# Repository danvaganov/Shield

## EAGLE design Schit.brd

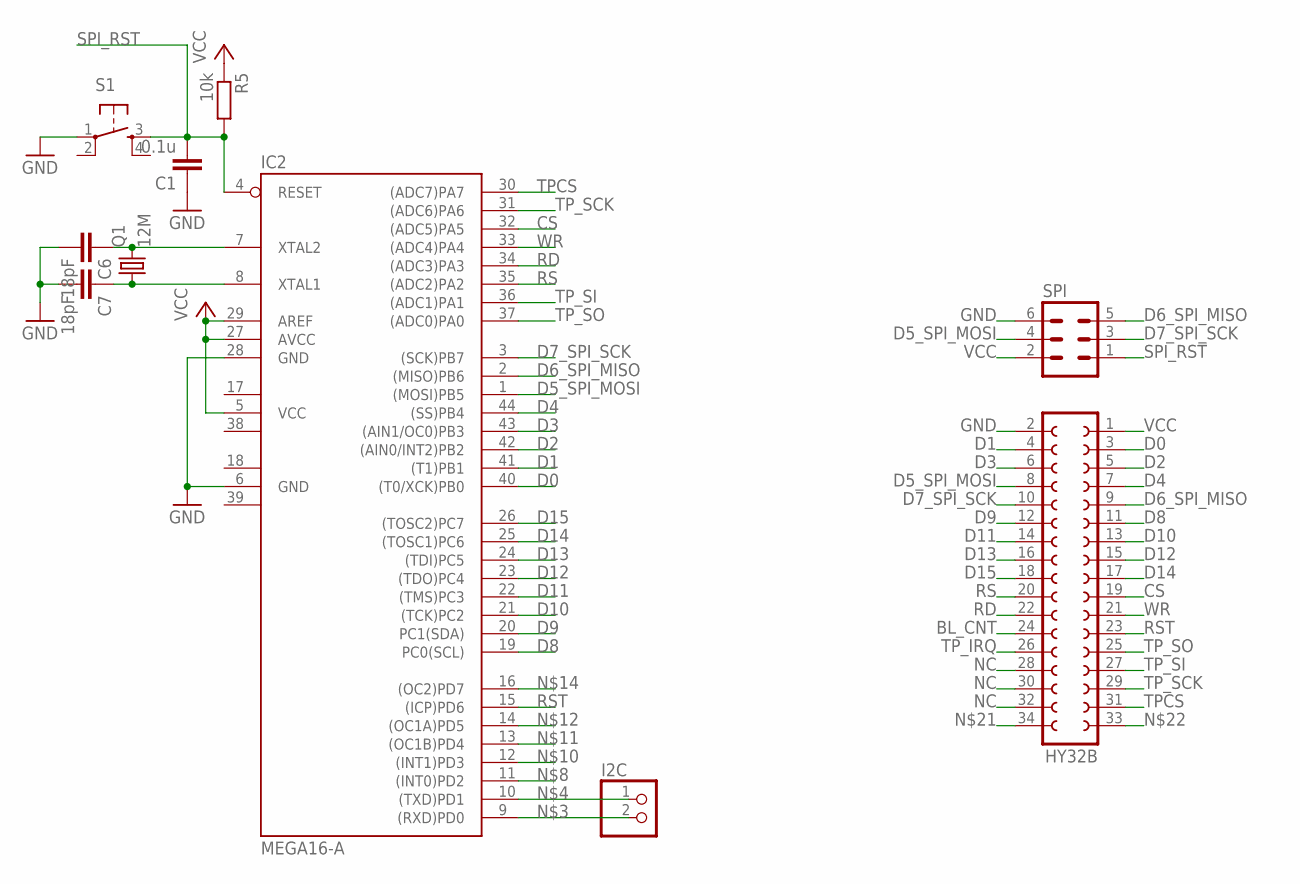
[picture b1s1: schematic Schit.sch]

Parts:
C1: 0.1u; C0805
C6, C7: 18pF; C0805
HY32B: FE17-2
I2C: PINHD-1X2; 1X02
IC2: MEGA16-A; TQFP44
Q1: 12M; HC49/S
R5: 10k; R0805
S1: TAC_SWITCHSMD; TACTILE_SWITCH_SMD
SPI: ML6

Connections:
BL_CNT: HY32B.24
CS: HY32B.19, IC2.32 ((ADC5)PA5)
D0: HY32B.3, IC2.40 ((T0/XCK)PB0)
D1: HY32B.4, IC2.41 ((T1)PB1)
D2: HY32B.5, IC2.42 ((AIN0/INT2)PB2)
D3: HY32B.6, IC2.43 ((AIN1/OC0)PB3)
D4: HY32B.7, IC2.44 ((SS)PB4)
D5_SPI_MOSI: HY32B.8, IC2.1 ((MOSI)PB5), SPI.4
D6_SPI_MISO: HY32B.9, IC2.2 ((MISO)PB6), SPI.5
D7_SPI_SCK: HY32B.10, IC2.3 ((SCK)PB7), SPI.3
D8: HY32B.11, IC2.19 (PC0(SCL))
D9: HY32B.12, IC2.20 (PC1(SDA))
D10: HY32B.13, IC2.21 ((TCK)PC2)
D11: HY32B.14, IC2.22 ((TMS)PC3)
D12: HY32B.15, IC2.23 ((TDO)PC4)
D13: HY32B.16, IC2.24 ((TDI)PC5)
D14: HY32B.17, IC2.25 ((TOSC1)PC6)
D15: HY32B.18, IC2.26 ((TOSC2)PC7)
GND: C1.1, C6.2, C7.2, HY32B.2, IC2.6 (GND), IC2.28 (GND), S1.1, SPI.6
GND1: IC2.18 (GND1)
GND2: IC2.39 (GND2)
unnamed: I2C.2, IC2.9 ((RXD)PD0)
unnamed: I2C.1, IC2.10 ((TXD)PD1)
unnamed: C7.1, IC2.8 (XTAL1), Q1.1
NC: HY32B.28, HY32B.30, HY32B.32
RD: HY32B.22, IC2.34 ((ADC3)PA3)
RS: HY32B.20, IC2.35 ((ADC2)PA2)
RST: HY32B.23, IC2.15 ((ICP)PD6)
SPI_RST: C1.2, IC2.4 (RESET), R5.2, S1.3, SPI.1
TPCS: HY32B.31, IC2.30 ((ADC7)PA7)
TP_IRQ: HY32B.26
TP_SCK: HY32B.29, IC2.31 ((ADC6)PA6)
TP_SI: HY32B.27, IC2.36 ((ADC1)PA1)
TP_SO: HY32B.25, IC2.37 ((ADC0)PA0)
VCC: HY32B.1, IC2.5 (VCC), IC2.27 (AVCC), IC2.29 (AREF), R5.1, SPI.2
VCC1: IC2.17 (VCC1)
VCC2: IC2.38 (VCC2)
WR: HY32B.21, IC2.33 ((ADC4)PA4)
XTAL1: C6.1, IC2.7 (XTAL2), Q1.2

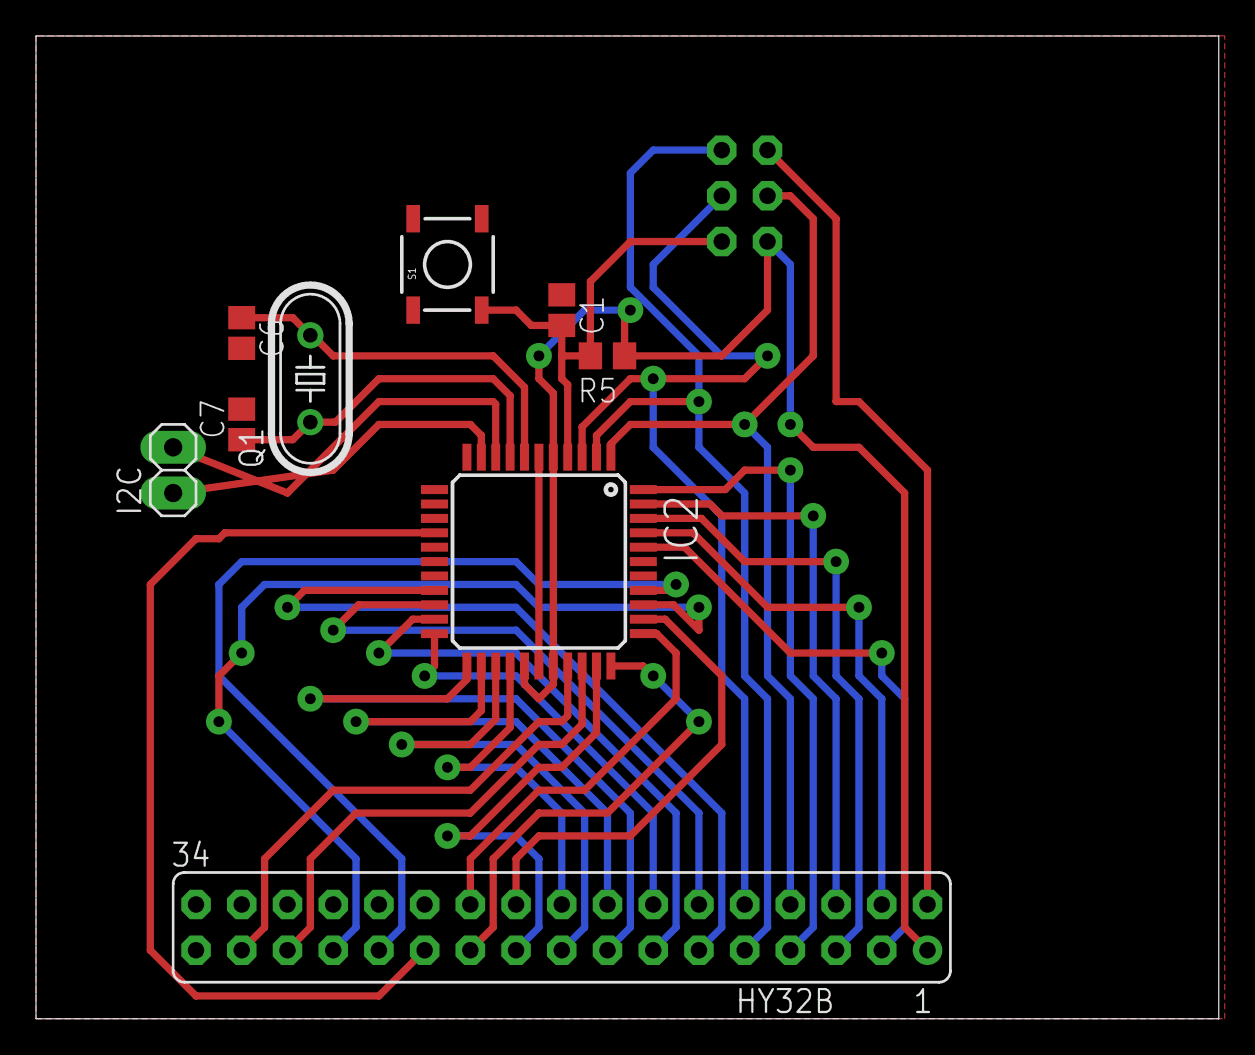
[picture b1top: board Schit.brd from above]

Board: 2 copper layers, 65.7 x 54.6 mm, 10 parts (1 on the bottom side), 33 nets.

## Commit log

2014-03-13 Shield with ATmega16A
2014-03-13 change mc to ATMega64A
2014-03-13 change mc to ATmega128A
2014-04-02 1.0.1

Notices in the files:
parts and their libraries:
SparkFun-Electromechanical: Licensing: CC v3.0 Share-Alike You are welcome to use this library for commercial purposes.
